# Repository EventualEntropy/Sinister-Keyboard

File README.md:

# Sinister-Keyboard
 A Lefty Compact 1800 style keyboard

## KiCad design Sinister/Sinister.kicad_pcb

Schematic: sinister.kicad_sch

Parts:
C1, C2, C3, C7: 100n; C_0402_1005Metric
C4, C8: 4.7u; C_0402_1005Metric
C5: 1u; C_0402_1005Metric
C6: 10n; C_0402_1005Metric
C9: 100u; C_0805_2012Metric_Pad1.15x1.40mm_HandSolder
C10: 10u; C_0805_2012Metric_Pad1.15x1.40mm_HandSolder
C11, C12, C15, C16, C17, C18, C19, C20, C21, C22, C23, C24, C25, C26, C27, C28, C29, C30: 1u; C_0805_2012Metric_Pad1.15x1.40mm_HandSolder
C13, C14: 100n; C_0805_2012Metric_Pad1.15x1.40mm_HandSolder
D1, D2, D3, D4, D5, D6, D7, D8, D9, D10, D11, D12, D13, D14, D15, D16, D17, D18, D19, D20, D21, D22, D23, D24, D25, D26, D27, D28, D29, D30, D31, D32, D33, D34, D35, D36, D37, D38, D39, D40, D41, D42, D43, D44, D45, D46, D47, D48, D49, D50, D51, D52, D53, D54, D55, D56, D57, D58, D59, D60, D61, D62, D63, D64, D65, D66, D67, D68, D69, D70, D71, D72, D73, D74, D75, D76, D77, D78, D79, D80, D81, D82, D83, D84, D85: 1N4148W; D_SOD-123
D86: RB060M-60TR; D_SOD-123; MANUFACTURER PART NUMBER RB060M-60TR; LCSC PART NUMBER C114257
D87: SMF9.0CA; D_SOD-123_Bidirectional; MANUFACTURER PART NUMBER SMF9.0CA; LCSC PART NUMBER C435473
D88, D89, D90, D91, D92, D93, D94, D95, D96, D97, D98, D99, D100, D101, D102, D103: WS2812C; LED_WS2812B_5.0x5.0mm_P3.2mm; MANUFACTURER PART NUMBER WS2812C; LCSC PART NUMBER\ C114587
F1: RF1338-000; Fuse_1812_4532Metric_Pad1.30x3.40mm_HandSolder; MANUFACTURER PART NUMBER RF-1338-000; LCSC PART NUMBER C207188
J1: TYPE-C-31-M12_13; TYPE-C-31-M-12
J2: Conn_ARM_JTAG_SWD_10
LED1, LED2, LED3, LED4, LED5, LED6, LED7, LED8, LED9, LED10, LED11, LED12, LED13, LED14, LED15, LED16, LED17, LED18, LED19, LED20, LED21, LED22, LED23, LED24, LED25, LED26, LED27, LED28, LED29, LED30, LED31, LED32, LED33, LED34, LED35, LED36, LED37, LED38, LED39, LED40, LED41, LED42, LED43, LED44, LED45, LED46, LED47, LED48, LED49, LED50, LED51, LED52, LED53, LED54, LED55, LED56, LED57, LED58, LED59, LED60, LED61, LED62, LED63, LED64, LED65, LED66, LED67, LED68, LED69, LED70, LED71, LED72, LED73, LED74, LED75, LED76, LED77, LED78, LED79, LED80, LED81, LED82, LED83, LED84: LED; LED_THT_2.54mm
Q1: AO3401A; SOT-23
Q2, Q3: DTC123JKAT146; SOT-23; MANUFACTURER PART NUMBER DTC123JKAT146; LCSC PART NUMBER C111724
Q4: AO3401A; SOT-23; MANUFACTURER PART NUMBER AO3401A; LCSC PART NUMBER C15127
R1: 33k; R_SMD_1206
R2, R104, R106: 10k; R_SMD_1206
R3, R25: 100R; R_SMD_1206
R4, R45, R46: 100k; R_SMD_1206
R5, R6, R7, R8, R9, R10, R11, R12, R13, R14, R15, R16, R17, R18, R19, R20, R21, R22, R23, R27, R28, R29, R30, R31, R32, R33, R34, R35, R36, R37, R38, R39, R40, R41, R42, R43, R44, R47, R48, R49, R50, R51, R52, R53, R54, R55, R56, R57, R58, R59, R60, R61, R62, R63, R64, R67, R68, R69, R70, R71, R72, R73, R74, R75, R76, R77, R78, R79, R80, R81, R82, R83, R84, R85, R86, R87, R88, R89, R90, R91, R92, R93, R94, R95: 390R; R_SMD_1206
R24, R26: 5.1k; R_0402_1005Metric
R65, R66: 1M; R_SMD_1206
R96, R97, R98, R99, R100, R101, R102, R103, R107, R108, R109, R110, R111, R112, R113, R114: 3R; R_SMD_1206
R105: 5.1k; R_SMD_1206
SW1, SW17: MINUS; MX100
SW2, SW70: FSLASH; MX100
SW3: ASTERISK; MX100
SW4: NUM LOCK; MX100
SW5: HOME; MX100
SW6: ESC; MX100
SW7: 1; MX100
SW8: 2; MX100
SW9: 3; MX100
SW10: 4; MX100
SW11: 5; MX100
SW12: 6; MX100
SW13: 7; MX100
SW14: 8; MX100
SW15: 9; MX100
SW16: 0; MX100
SW18: PLUS; MX100
SW19: BKSP; MX200R
SW20: NUM 7; MX100
SW21: NUM 8; MX100
SW22: NUM 9; MX100
SW23: END; MX100
SW24: TAB; MX150
SW25: Q; MX100
SW26: W; MX100
SW27: E; MX100
SW28: R; MX100
SW29: T; MX100
SW30: Y; MX100
SW31: U; MX100
SW32: I; MX100
SW33: O; MX100
SW34: P; MX100
SW35: LBRKT; MX100
SW36: RBRKT; MX100
SW37: BSLASH; MX150
SW38: NUM PLUS; MX200VR
SW39: NUM4; MX100
SW40: NUM5; MX100
SW41: NUM 6; MX100
SW42: DEL; MX100
SW43: CAPSLOCK; MX175
SW44: A; MX100
SW45: S; MX100
SW46: D; MX100
SW47: F; MX100
SW48: G; MX100
SW49: H; MX100
SW50: J; MX100
SW51: K; MX100
SW52: L; MX100
SW53: COLON; MX100
SW54: QUOTE; MX100
SW55: ENTER; MX225
SW56: NUM 1; MX100
SW57: NUM 2; MX100
SW58: NUM 3; MX100
SW59: UP; MX100
SW60: LSHIFT; MX225R
SW61: Z; MX100
SW62: X; MX100
SW63: C; MX100
SW64: V; MX100
SW65: B; MX100
SW66: N; MX100
SW67: M; MX100
SW68: COMMA; MX100
SW69: PERIOD; MX100
SW71: RSHIFT; MX275R
SW72: NUM ENTER; MX200VR
SW73: NUM PERIOD; MX100
SW74: NUM 0; MX100
SW75: LEFT; MX100
SW76: DOWN; MX100
SW77: RIGHT; MX100
SW78: LCTRL; MX150
SW79: LALT; MX125
SW80: SPACE; MX625R
SW81: RALT; MX125
SW82: MENU; MX125
SW83: FN; MX125
SW84: RCRTL; MX125
SW85: K2-1187SQ-A4SW-06; MANUFACTURER PART NUMBER K2-1187SQ-A4SW-06; LCSC PART NUMBER C92584
U1: STM32F072-LQFP48; LQFP-48_7x7mm_P0.5mm
U2: MCP1700-3302E_SOT23; SOT-23; MANUFACTURER PART NUMBER MCP1700-3302E/TT; LCSC PART NUMBER C39051
U3: TPD4E05U06DQAR; USON-10_2.5x1.0mm_P0.5mm; Manufacturer Part # TPD4E05U06DQAR; LCSC Part # C138714

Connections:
3V3: C1.1, C2.2, C3.2, C4.2, C5.2, C6.2, C7.2, C8.2, C11.1, D86.2 (A), J2.1 (VCC), R45.1, SW85.1, U1.1 (VBAT), U1.9 (VDDA), U1.24 (VDD), U1.36 (VDDIO2), U1.48 (VDD), U2.2 (VO)
5V: C12.1, D86.1 (K), D87.1 (A1), F1.2, Q1.2 (S), R2.1, R46.1, R96.1, R97.1, R98.1, R99.1, R100.1, R101.1, R102.1, R103.1, R104.1, R105.1, R107.1, R108.1, R109.1, R110.2, R111.1, R112.1, R113.1, R114.1, U2.3 (VI)
BOOT0: C9.1, R1.1, R4.1, U1.44 (BOOT0)
COL0: SW1.1 (Col), SW38.1 (Col), SW72.1 (Col)
COL1: SW2.1 (Col), SW20.1 (Col), SW39.1 (Col), SW56.1 (Col), SW73.1 (Col)
COL2: SW3.1 (Col), SW21.1 (Col), SW40.1 (Col), SW57.1 (Col), SW74.1 (Col)
COL3: SW4.1 (Col), SW22.1 (Col), SW41.1 (Col), SW58.1 (Col), SW75.1 (Col)
COL4: SW5.1 (Col), SW23.1 (Col), SW42.1 (Col), SW59.1 (Col), SW76.1 (Col)
COL5: SW6.1 (Col), SW24.1 (Col), SW43.1 (Col), SW60.1 (Col), SW77.1 (Col)
COL6: SW7.1 (Col), SW25.1 (Col), SW44.1 (Col), SW61.1 (Col), SW78.1 (Col)
COL7: SW8.1 (Col), SW26.1 (Col), SW45.1 (Col), SW62.1 (Col), SW79.1 (Col)
COL8: SW9.1 (Col), SW27.1 (Col), SW46.1 (Col), SW63.1 (Col)
COL9: SW10.1 (Col), SW28.1 (Col), SW47.1 (Col), SW64.1 (Col)
COL10: SW11.1 (Col), SW29.1 (Col), SW48.1 (Col), SW65.1 (Col), SW80.1 (Col)
COL11: SW12.1 (Col), SW30.1 (Col), SW49.1 (Col), SW66.1 (Col)
COL12: SW13.1 (Col), SW31.1 (Col), SW50.1 (Col), SW67.1 (Col)
COL13: SW14.1 (Col), SW32.1 (Col), SW51.1 (Col), SW68.1 (Col), SW81.1 (Col)
COL14: SW15.1 (Col), SW33.1 (Col), SW52.1 (Col), SW69.1 (Col)
COL15: SW16.1 (Col), SW34.1 (Col), SW53.1 (Col), SW70.1 (Col), SW82.1 (Col)
COL16: SW17.1 (Col), SW35.1 (Col), SW54.1 (Col), SW71.1 (Col), SW83.1 (Col)
COL17: SW18.1 (Col), SW36.1 (Col), SW55.1 (Col), SW84.1 (Col)
COL18: SW19.1 (Col), SW37.1 (Col)
D+: J1.A6 (D+), J1.B6 (D+), U1.33 (USB_DP/PA12), U3.2 (IO2), U3.5 (D2-), U3.6 (NC), U3.9 (NC)
D-: J1.A7 (D-), J1.B7 (D-), U1.32 (USB_DM/TIM1_CH4/PA11), U3.1 (IO1), U3.4 (D2+), U3.7 (NC), U3.10 (NC)
GND: C1.2, C2.1, C3.1, C4.1, C5.1, C6.1, C7.1, C8.1, C9.2, C10.2, C11.2, C12.2, C13.2, C14.2, C15.2, C16.2, C17.2, C18.2, C19.2, C20.2, C21.2, C22.2, C23.2, C24.2, C25.2, C26.2, C27.2, C28.2, C29.2, C30.2, D87.2 (A2), D88.3 (VSS), D89.3 (VSS), D90.3 (VSS), D91.3 (VSS), D92.3 (VSS), D93.3 (VSS), D94.3 (VSS), D95.3 (VSS), D96.3 (VSS), D97.3 (VSS), D98.3 (VSS), D99.3 (VSS), D100.3 (VSS), D101.3 (VSS), D102.3 (VSS), D103.3 (VSS), J1.A1 (GND), J1.B1 (GND), J2.3 (GND), J2.5 (GND), J2.9 (GNDDetect), LED1.K, LED2.K, LED3.K, LED4.K, LED5.K, LED6.K, LED7.K, LED8.K, LED9.K, LED10.K, LED11.K, LED12.K, LED13.K, LED14.K, LED15.K, LED16.K, LED17.K, LED18.K, LED19.K, LED20.K, LED21.K, LED22.K, LED23.K, LED24.K, LED25.K, LED26.K, LED27.K, LED28.K, LED29.K, LED30.K, LED31.K, LED32.K, LED33.K, LED34.K, LED35.K, LED36.K, LED37.K, LED38.K, LED39.K, LED40.K, LED41.K, LED42.K, LED43.K, LED44.K, LED45.K, LED46.K, LED47.K, LED48.K, LED49.K, LED50.K, LED51.K, LED52.K, LED53.K, LED54.K, LED55.K, LED56.K, LED57.K, LED58.K, LED59.K, LED60.K, LED61.K, LED62.K, LED63.K, LED64.K, LED65.K, LED66.K, LED67.K, LED68.K, LED69.K, LED70.K, LED71.K, LED72.K, LED73.K, LED74.K, LED75.K, LED76.K, LED77.K, LED78.K, LED79.K, LED80.K, LED81.K, LED82.K, LED83.K, LED84.K, Q2.2 (E), Q3.2 (E), R4.2, R24.2, R26.2, R45.2, R46.2, R65.1, R66.1, R106.2, U1.8 (VSSA), U1.23 (VSS), U1.35 (VSS), U1.47 (VSS), U2.1 (GND), U3.3 (GND), U3.8 (GND)
LED_PWM: Q2.1 (B), U1.16 (PA6/ADC_IN6/TIM3_CH1/TIM16_CH1)
unnamed: C13.1, C14.1, J1.S (SHIELD), R65.2, R66.2
unnamed: C15.1, D88.1 (VDD), R96.2
unnamed: C16.1, D89.1 (VDD), R97.2
unnamed: C17.1, D90.1 (VDD), R98.2
unnamed: C18.1, D91.1 (VDD), R99.2
unnamed: C19.1, D92.1 (VDD), R100.2
unnamed: C20.1, D93.1 (VDD), R101.2
unnamed: C21.1, D94.1 (VDD), R102.2
unnamed: C22.1, D95.1 (VDD), R103.2
unnamed: C23.1, D96.1 (VDD), R107.2
unnamed: C24.1, D97.1 (VDD), R108.2
unnamed: C25.1, D98.1 (VDD), R109.2
unnamed: C26.1, D99.1 (VDD), R110.1
unnamed: C27.1, D100.1 (VDD), R111.2
unnamed: C28.1, D101.1 (VDD), R112.2
unnamed: C29.1, D102.1 (VDD), R113.2
unnamed: C30.1, D103.1 (VDD), R114.2
unnamed: D1.2 (A), SW1.2 (Row)
unnamed: D2.2 (A), SW2.2 (Row)
unnamed: D3.2 (A), SW3.2 (Row)
unnamed: D4.2 (A), SW4.2 (Row)
unnamed: D5.2 (A), SW5.2 (Row)
unnamed: D6.2 (A), SW6.2 (Row)
unnamed: D7.2 (A), SW7.2 (Row)
unnamed: D8.2 (A), SW8.2 (Row)
unnamed: D9.2 (A), SW9.2 (Row)
unnamed: D10.2 (A), SW10.2 (Row)
unnamed: D11.2 (A), SW11.2 (Row)
unnamed: D12.2 (A), SW12.2 (Row)
unnamed: D13.2 (A), SW13.2 (Row)
unnamed: D14.2 (A), SW14.2 (Row)
unnamed: D15.2 (A), SW15.2 (Row)
unnamed: D16.2 (A), SW16.2 (Row)
unnamed: D17.2 (A), SW17.2 (Row)
unnamed: D18.2 (A), SW18.2 (Row)
unnamed: D19.2 (A), SW19.2 (Row)
unnamed: D20.2 (A), SW20.2 (Row)
unnamed: D21.2 (A), SW21.2 (Row)
unnamed: D22.2 (A), SW22.2 (Row)
unnamed: D23.2 (A), SW23.2 (Row)
unnamed: D24.2 (A), SW24.2 (Row)
unnamed: D25.2 (A), SW25.2 (Row)
unnamed: D26.2 (A), SW26.2 (Row)
unnamed: D27.2 (A), SW27.2 (Row)
unnamed: D28.2 (A), SW28.2 (Row)
unnamed: D29.2 (A), SW29.2 (Row)
unnamed: D30.2 (A), SW30.2 (Row)
unnamed: D31.2 (A), SW31.2 (Row)
unnamed: D32.2 (A), SW32.2 (Row)
unnamed: D33.2 (A), SW33.2 (Row)
unnamed: D34.2 (A), SW34.2 (Row)
unnamed: D35.2 (A), SW35.2 (Row)
unnamed: D36.2 (A), SW36.2 (Row)
unnamed: D37.2 (A), SW37.2 (Row)
unnamed: D38.2 (A), SW38.2 (Row)
unnamed: D39.2 (A), SW39.2 (Row)
unnamed: D40.2 (A), SW40.2 (Row)
unnamed: D41.2 (A), SW41.2 (Row)
unnamed: D42.2 (A), SW42.2 (Row)
unnamed: D43.2 (A), SW43.2 (Row)
unnamed: D44.2 (A), SW44.2 (Row)
unnamed: D45.2 (A), SW45.2 (Row)
unnamed: D46.2 (A), SW46.2 (Row)
unnamed: D47.2 (A), SW47.2 (Row)
unnamed: D48.2 (A), SW48.2 (Row)
unnamed: D49.2 (A), SW49.2 (Row)
unnamed: D50.2 (A), SW50.2 (Row)
unnamed: D51.2 (A), SW51.2 (Row)
unnamed: D52.2 (A), SW52.2 (Row)
unnamed: D53.2 (A), SW53.2 (Row)
unnamed: D54.2 (A), SW54.2 (Row)
unnamed: D55.2 (A), SW55.2 (Row)
unnamed: D56.2 (A), SW56.2 (Row)
unnamed: D57.2 (A), SW57.2 (Row)
unnamed: D58.2 (A), SW58.2 (Row)
unnamed: D59.2 (A), SW59.2 (Row)
unnamed: D60.2 (A), SW60.2 (Row)
unnamed: D61.2 (A), SW61.2 (Row)
unnamed: D62.2 (A), SW62.2 (Row)
unnamed: D63.2 (A), SW63.2 (Row)
unnamed: D64.2 (A), SW64.2 (Row)
unnamed: D65.2 (A), SW65.2 (Row)
unnamed: D66.2 (A), SW66.2 (Row)
unnamed: D67.2 (A), SW67.2 (Row)
unnamed: D68.2 (A), SW68.2 (Row)
unnamed: D69.2 (A), SW69.2 (Row)
unnamed: D70.2 (A), SW70.2 (Row)
unnamed: D71.2 (A), SW71.2 (Row)
unnamed: D72.2 (A), SW72.2 (Row)
unnamed: D73.2 (A), SW73.2 (Row)
unnamed: D74.2 (A), SW74.2 (Row)
unnamed: D75.2 (A), SW75.2 (Row)
unnamed: D76.2 (A), SW76.2 (Row)
unnamed: D77.2 (A), SW77.2 (Row)
unnamed: D78.2 (A), SW78.2 (Row)
unnamed: D79.2 (A), SW79.2 (Row)
unnamed: D80.2 (A), SW80.2 (Row)
unnamed: D81.2 (A), SW81.2 (Row)
unnamed: D82.2 (A), SW82.2 (Row)
unnamed: D83.2 (A), SW83.2 (Row)
unnamed: D84.2 (A), SW84.2 (Row)
unnamed: D85.1 (K), R1.2
unnamed: D85.2 (A), Q3.1 (B), SW85.2
unnamed: D88.2 (DOUT), D89.4 (DIN)
unnamed: D89.2 (DOUT), D90.4 (DIN)
unnamed: D90.2 (DOUT), D91.4 (DIN)
unnamed: D91.2 (DOUT), D92.4 (DIN)
unnamed: D92.2 (DOUT), D93.4 (DIN)
unnamed: D93.2 (DOUT), D94.4 (DIN)
unnamed: D94.2 (DOUT), D95.4 (DIN)
unnamed: D96.2 (DOUT), D97.4 (DIN)
unnamed: D97.2 (DOUT), D98.4 (DIN)
unnamed: D98.2 (DOUT), D99.4 (DIN)
unnamed: D100.2 (DOUT), D101.4 (DIN)
unnamed: D99.2 (DOUT), D100.4 (DIN)
unnamed: D101.2 (DOUT), D102.4 (DIN)
unnamed: D102.2 (DOUT), D103.4 (DIN)
unnamed: J1.A5 (CC1), R24.1
unnamed: J1.B5 (CC2), R26.1
unnamed: LED1.A, R5.1
unnamed: LED2.A, R6.1
unnamed: LED3.A, R7.1
unnamed: LED4.A, R8.1
unnamed: LED5.A, R9.1
unnamed: LED6.A, R10.1
unnamed: LED7.A, R11.1
unnamed: LED8.A, R12.1
unnamed: LED9.A, R13.1
unnamed: LED10.A, R14.1
unnamed: LED11.A, R15.1
unnamed: LED12.A, R16.1
unnamed: LED13.A, R17.1
unnamed: LED14.A, R18.1
unnamed: LED15.A, R19.1
unnamed: LED16.A, R20.1
unnamed: LED17.A, R21.1
unnamed: LED18.A, R22.1
unnamed: LED19.A, R23.1
unnamed: LED20.A, R27.1
unnamed: LED21.A, R28.1
unnamed: LED22.A, R29.1
unnamed: LED23.A, R30.1
unnamed: LED24.A, R31.1
unnamed: LED25.A, R32.1
unnamed: LED26.A, R33.1
unnamed: LED27.A, R34.1
unnamed: LED28.A, R35.1
unnamed: LED29.A, R36.1
unnamed: LED30.A, R37.1
unnamed: LED31.A, R38.1
unnamed: LED32.A, R39.1
unnamed: LED33.A, R40.1
unnamed: LED34.A, R41.1
unnamed: LED35.A, R42.1
unnamed: LED36.A, R43.1
unnamed: LED37.A, R44.1
unnamed: LED38.A, R47.1
unnamed: LED39.A, R48.1
unnamed: LED40.A, R49.1
unnamed: LED41.A, R50.1
unnamed: LED42.A, R51.1
unnamed: LED43.A, R52.1
unnamed: LED44.A, R53.1
unnamed: LED45.A, R54.1
unnamed: LED46.A, R55.1
unnamed: LED47.A, R56.1
unnamed: LED48.A, R57.1
unnamed: LED49.A, R58.1
unnamed: LED50.A, R59.1
unnamed: LED51.A, R60.1
unnamed: LED52.A, R61.1
unnamed: LED53.A, R62.1
unnamed: LED54.A, R63.1
unnamed: LED55.A, R64.1
unnamed: LED56.A, R67.1
unnamed: LED57.A, R68.1
unnamed: LED58.A, R69.1
unnamed: LED59.A, R70.1
unnamed: LED60.A, R71.1
unnamed: LED61.A, R72.1
unnamed: LED62.A, R73.1
unnamed: LED63.A, R74.1
unnamed: LED64.A, R75.1
unnamed: LED65.A, R76.1
unnamed: LED66.A, R77.1
unnamed: LED67.A, R78.1
unnamed: LED68.A, R79.1
unnamed: LED69.A, R80.1
unnamed: LED70.A, R81.1
unnamed: LED71.A, R82.1
unnamed: LED72.A, R83.1
unnamed: LED73.A, R84.1
unnamed: LED74.A, R85.1
unnamed: LED75.A, R86.1
unnamed: LED76.A, R87.1
unnamed: LED77.A, R88.1
unnamed: LED78.A, R89.1
unnamed: LED79.A, R90.1
unnamed: LED80.A, R91.1
unnamed: LED81.A, R92.1
unnamed: LED82.A, R93.1
unnamed: LED83.A, R94.1
unnamed: LED84.A, R95.1
unnamed: Q1.1 (G), R3.1
unnamed: Q1.3 (D), R5.2, R6.2, R7.2, R8.2, R9.2, R10.2, R11.2, R12.2, R13.2, R14.2, R15.2, R16.2, R17.2, R18.2, R19.2, R20.2, R21.2, R22.2, R23.2, R27.2, R28.2, R29.2, R30.2, R31.2, R32.2, R33.2, R34.2, R35.2, R36.2, R37.2, R38.2, R39.2, R40.2, R41.2, R42.2, R43.2, R44.2, R47.2, R48.2, R49.2, R50.2, R51.2, R52.2, R53.2, R54.2, R55.2, R56.2, R57.2, R58.2, R59.2, R60.2, R61.2, R62.2, R63.2, R64.2, R67.2, R68.2, R69.2, R70.2, R71.2, R72.2, R73.2, R74.2, R75.2, R76.2, R77.2, R78.2, R79.2, R80.2, R81.2, R82.2, R83.2, R84.2, R85.2, R86.2, R87.2, R88.2, R89.2, R90.2, R91.2, R92.2, R93.2, R94.2, R95.2
unnamed: Q2.3 (C), R2.2, R3.2
unnamed: Q3.3 (C), R25.1
unnamed: Q4.1 (G), R105.2, R106.1
RGB8-RGB9: D95.2 (DOUT), D96.4 (DIN)
RGB_3V3: Q4.3 (D), U1.28 (SPI2_MOSI/I2S2_SD/PB15)
RGB_5V: D88.4 (DIN), Q4.2 (S), R104.2
ROW0: D1.1 (K), D2.1 (K), D3.1 (K), D4.1 (K), D5.1 (K), D6.1 (K), D7.1 (K), D8.1 (K), D9.1 (K), D10.1 (K), D11.1 (K), D12.1 (K), D13.1 (K), D14.1 (K), D15.1 (K), D16.1 (K), D17.1 (K), D18.1 (K), D19.1 (K)
ROW1: D20.1 (K), D21.1 (K), D22.1 (K), D23.1 (K), D24.1 (K), D25.1 (K), D26.1 (K), D27.1 (K), D28.1 (K), D29.1 (K), D30.1 (K), D31.1 (K), D32.1 (K), D33.1 (K), D34.1 (K), D35.1 (K), D36.1 (K), D37.1 (K)
ROW2: D38.1 (K), D39.1 (K), D40.1 (K), D41.1 (K), D42.1 (K), D43.1 (K), D44.1 (K), D45.1 (K), D46.1 (K), D47.1 (K), D48.1 (K), D49.1 (K), D50.1 (K), D51.1 (K), D52.1 (K), D53.1 (K), D54.1 (K), D55.1 (K)
ROW3: D56.1 (K), D57.1 (K), D58.1 (K), D59.1 (K), D60.1 (K), D61.1 (K), D62.1 (K), D63.1 (K), D64.1 (K), D65.1 (K), D66.1 (K), D67.1 (K), D68.1 (K), D69.1 (K), D70.1 (K), D71.1 (K)
ROW4: D72.1 (K), D73.1 (K), D74.1 (K), D75.1 (K), D76.1 (K), D77.1 (K), D78.1 (K), D79.1 (K), D80.1 (K), D81.1 (K), D82.1 (K), D83.1 (K), D84.1 (K)
SWCLK: J2.4 (SWDCLK/TCK), U1.37 (SWCLK/PA14)
SWDIO: J2.2 (SWDIO/TMS), U1.34 (SWDIO/PA13)
VBUS: F1.1, J1.A4 (VBUS), J1.B4 (VBUS)
nRST: C10.1, J2.10 (~RESET~), R25.2, U1.7 (NRST)

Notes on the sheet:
RBG
LEDs
SWITCH MATRIX
USB Connector
ESD Protection
LDO
JTAG SWD
MCU Reset
MCU

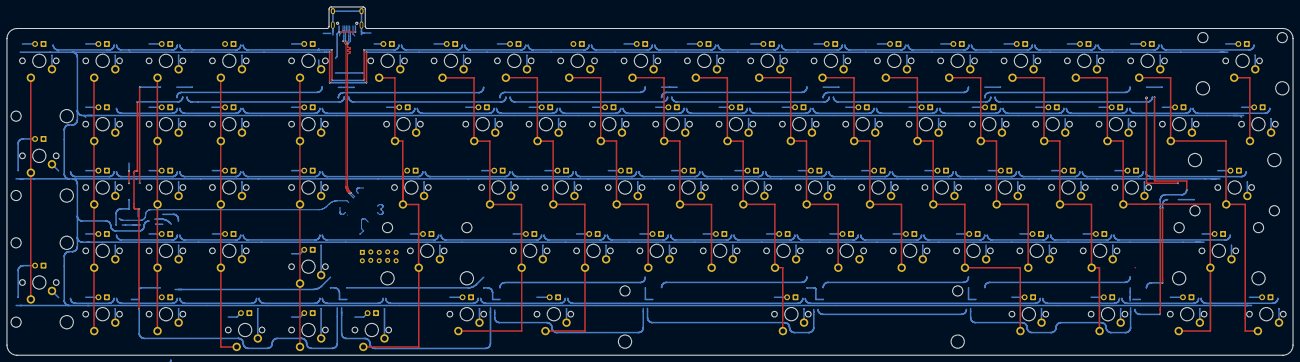
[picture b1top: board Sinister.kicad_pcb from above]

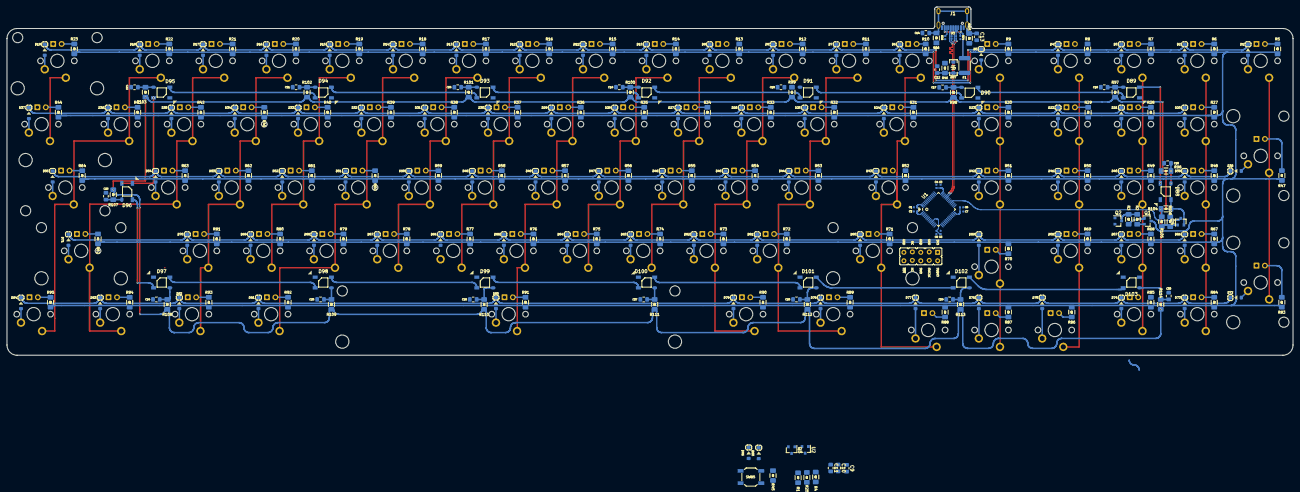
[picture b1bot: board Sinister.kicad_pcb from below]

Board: 2 copper layers, 386.8 x 104.7 mm, 426 parts (426 on the bottom side), 246 nets.

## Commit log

2020-07-04 Initialized Fresh KiCad project
    See above.
2020-07-04 Added Submodules
2020-07-04 Added Symbol and Footprint Libraries from the Acheron Project.
2020-07-04 Added and labelled switches and diodes for keymap.
2020-07-05 Added USB-C, ESD, and connected the matrix
    Connected matrix, removed swtiches from BOM, Added and connected USB-C as well as the ESD chip. Reconfigured paths for schematic symbols and footprint locations. Removed unnecessary footprint librari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
2020-07-05 Corrected schematic name
2020-07-06 Added ancilliary components to schematic.
    Added the LED array, USB connector, ESD protection, MCU reset circuit, LDO, and JTAG SWD. Added and connected necessary components for the MCU.
2020-07-16 Placed components and routed matrixes.
    Placed LED resistors and keyswitch diodes. Routed LED and keyswitch matrixes. Repositioned labels for clarity and organization.
2020-07-16 pushed for Gondo Help
    Trying to length match USBC data lines
2020-07-23 Began placing and routing power and RGB components.
    Placed and routed: RGB caps and resistors, MCU caps, VBUS components.
2020-07-24 Placed and routed reaminder of RGB components.
    Repositioned RGB components, rereouted RGB connections. Rerouted Columns.
2020-07-24 Rereouted diodes. Placed LED components.
    Replaced diodes tracks. Placed and routed LED power components. Routed 5V RGB tracks.
2020-08-04 Began routing Rows and Columns. Added Indicator LEDs.
    Finished routing Rows, Halfway through routing Columns. Added and routed Indicator lights for Num Lock, Caps Lock, and Layers 1-3. Added GND and 3V3 pours and islands.
2020-08-06 Finished routing tracks, Ran DRC, resolved errors.
    Finished routing the final 10 columns to the MCU. Ran DRC and resolved errors. 1 pad size error for USBC and two warnings for unconnected trakcs that are cosmetic are all that remain.
    Still to do: Silkscreen.
2020-08-06 Resolved 2 warnings in DRC
    Resolved the two "Unconnected tracks" warnings in the DRC.
2020-08-14 Retraced bent routes.
    KiCad Nightly did not like copied and pasted bent tracks and was not exporting them to Gerbers properly. Retraced and bent all copied and pasted tracks.
2020-08-15 Created and placed Logo footprint.
    Created and placed Logo footprint.
2020-08-16 Organized Bottom Silkscreen layer. Added Logo.
    Reorganized bottom silkscreen layer for clarity. Resized all references for uniform size. Added stylized SINISTER logo to bottom copper layer.
2020-08-22 Repaired Logo. Added Solenoid.
    Repaired problematic polygons on the Logo that were causing incorrect line thickness during loads from save file. Added and routed components for external solenoid. Finished BOM xlsx.
